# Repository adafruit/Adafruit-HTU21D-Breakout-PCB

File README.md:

## Adafruit HTU21D Breakout PCB
<a href="http://www.adafruit.com/products/1899"><br/>
<a href="http://www.adafruit.com/products/1899"><br/>
Click here to purchase one from the Adafruit shop</a>

The HTU21D-F Temperature + Humidity Sensor - the best way to prove the weatherman wrong!

This I2C digital humidity sensor is an accurate and intelligent alternative to the much simpler Humidity and Temperature Sensor - SHT15 Breakout It has a typical accuracy of ±2% with an operating range that's optimized from 5% to 95% RH. Operation outside this range is still possible - just the accuracy might drop a bit. The temperature output has an accuracy of ±1°C from -30~90°C. If you're looking to measure temperature more accurately, we recommend the MCP9808 High Accuracy I2C Temperature Sensor Breakout Board.

To get you going fast, we spun up a custom made PCB in the STEMMA QT form factor, making them easy to interface with. The STEMMA QT connectors on either side are compatible with the SparkFun Qwiic I2C connectors. This allows you to make solderless connections between your development board and the HTU21Ds or to chain them with a wide range of other sensors and accessories using a compatible cable. QT Cable is not included, but we have a variety in the shop.

PCB files for the Adafruit HTU21D Breakout. The format is EagleCAD schematic and board layout
- https://www.adafruit.com/products/1899

### License

Adafruit invests time and resources providing this open source design, please support Adafruit and open-source hardware by purchasing products from [Adafruit](https://www.adafruit.com)!

All text above must be included in any redistribution

Designed by Limor Fried/Ladyada for Adafruit Industries.
Creative Commons Attribution/Share-Alike, all text above must be included in any redistribution. 
See license.txt for additional information.

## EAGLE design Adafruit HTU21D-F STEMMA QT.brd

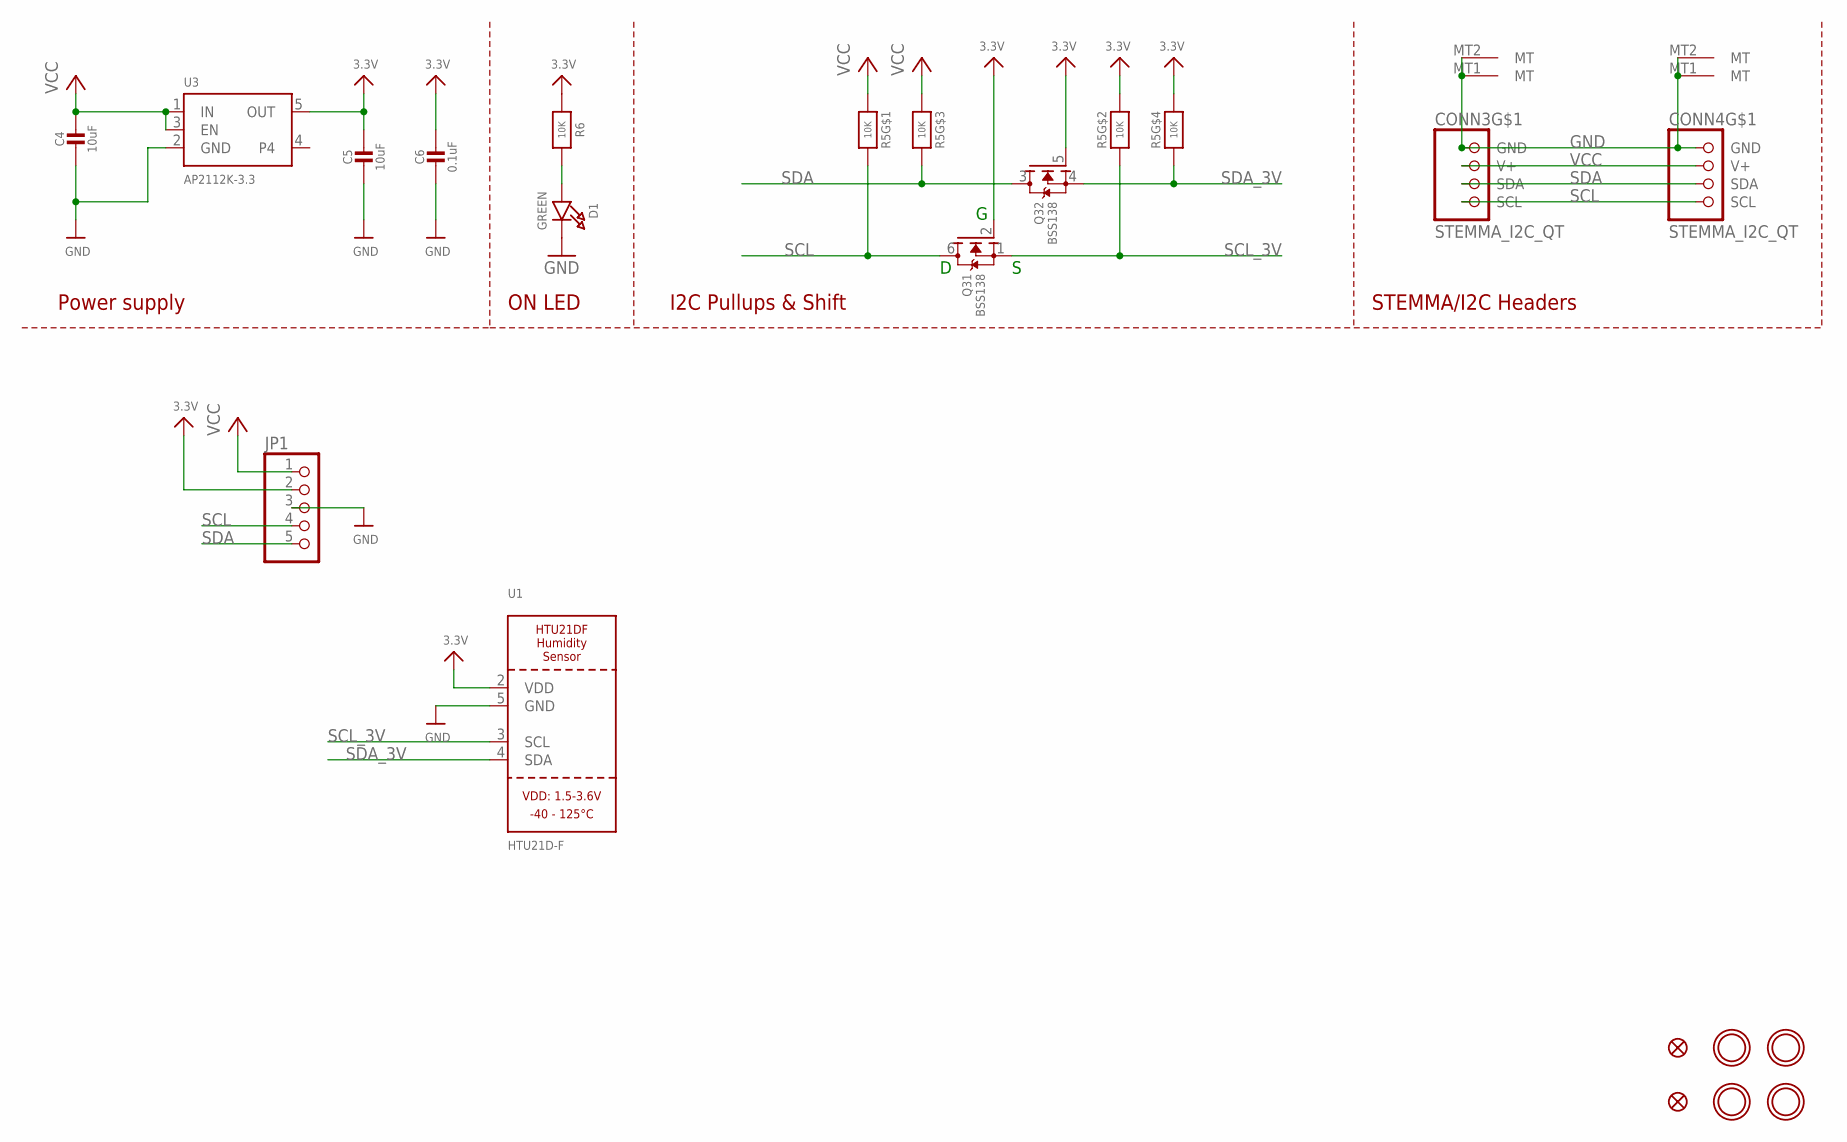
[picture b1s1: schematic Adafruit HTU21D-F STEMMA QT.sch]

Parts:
C4, C5: 10uF; 0805-NO
C6: 0.1uF; 0603-NO
CONN3, CONN4: STEMMA_I2C_QT; JST_SH4
D1: GREEN; CHIPLED_0603_NOOUTLINE
FID3, FID4: FIDUCIAL_1MM
JP1: HEADER-1X570MIL; 1X05_ROUND_70
Q3: BSS138; SOT363
R5: 10K; RESPACK_4X0603
R6: 10K; 0603-NO
U1: HTU21D-F; HTU21DF
U3: AP2112K-3.3; SOT23-5
U$19, U$20, U$22, U$25: MOUNTINGHOLE2.5; MOUNTINGHOLE_2.5_PLATED

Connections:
3.3V: C5.1, C6.1, JP1.2, Q3.2 (G), Q3.5 (G), R5.2 (1), R5.4 (1), R6.1, U1.2 (VDD), U3.5 (OUT)
GND: C4.2, C5.2, C6.2, CONN3.1 (GND), CONN3.MT1 (MT), CONN3.MT2 (MT), CONN4.1 (GND), CONN4.MT1 (MT), CONN4.MT2 (MT), D1.C, JP1.3, U1.5 (GND), U3.2 (GND)
unnamed: D1.A, R6.2
SCL: CONN3.4 (SCL), CONN4.4 (SCL), JP1.4, Q3.6 (D), R5.8 (2)
SCL_3V: Q3.1 (S), R5.7 (2), U1.3 (SCL)
SDA: CONN3.3 (SDA), CONN4.3 (SDA), JP1.5, Q3.3 (D), R5.6 (2)
SDA_3V: Q3.4 (S), R5.5 (2), U1.4 (SDA)
VCC: C4.1, CONN3.2 (V+), CONN4.2 (V+), JP1.1, R5.1, R5.3 (1), U3.1 (IN), U3.3 (EN)

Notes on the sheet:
I2C Pullups & Shift
STEMMA/I2C Headers
ON LED
Power supply

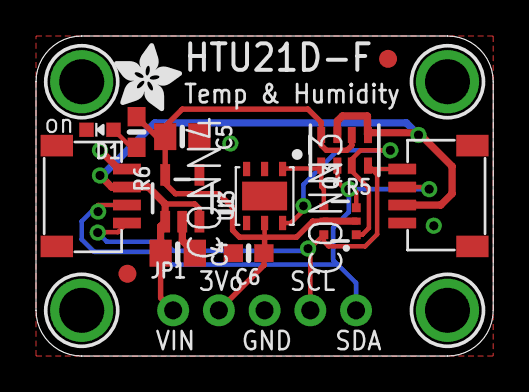
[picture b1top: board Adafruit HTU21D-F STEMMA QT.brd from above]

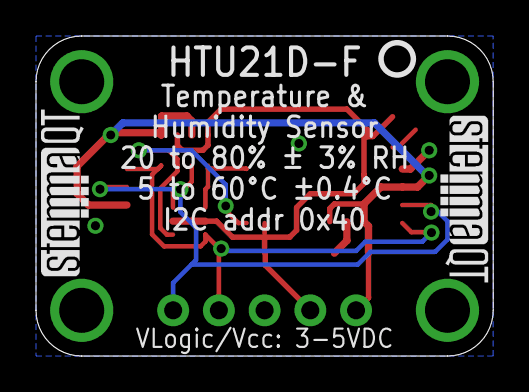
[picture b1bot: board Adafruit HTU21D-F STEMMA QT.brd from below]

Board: 2 copper layers, 25.4 x 17.8 mm, 22 parts (3 on the bottom side), 8 nets.

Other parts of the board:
U$28: ADAFRUIT_3.5MM
U$29: PCBFEAT-REV-040
U$30, U$31: STEMMAQT

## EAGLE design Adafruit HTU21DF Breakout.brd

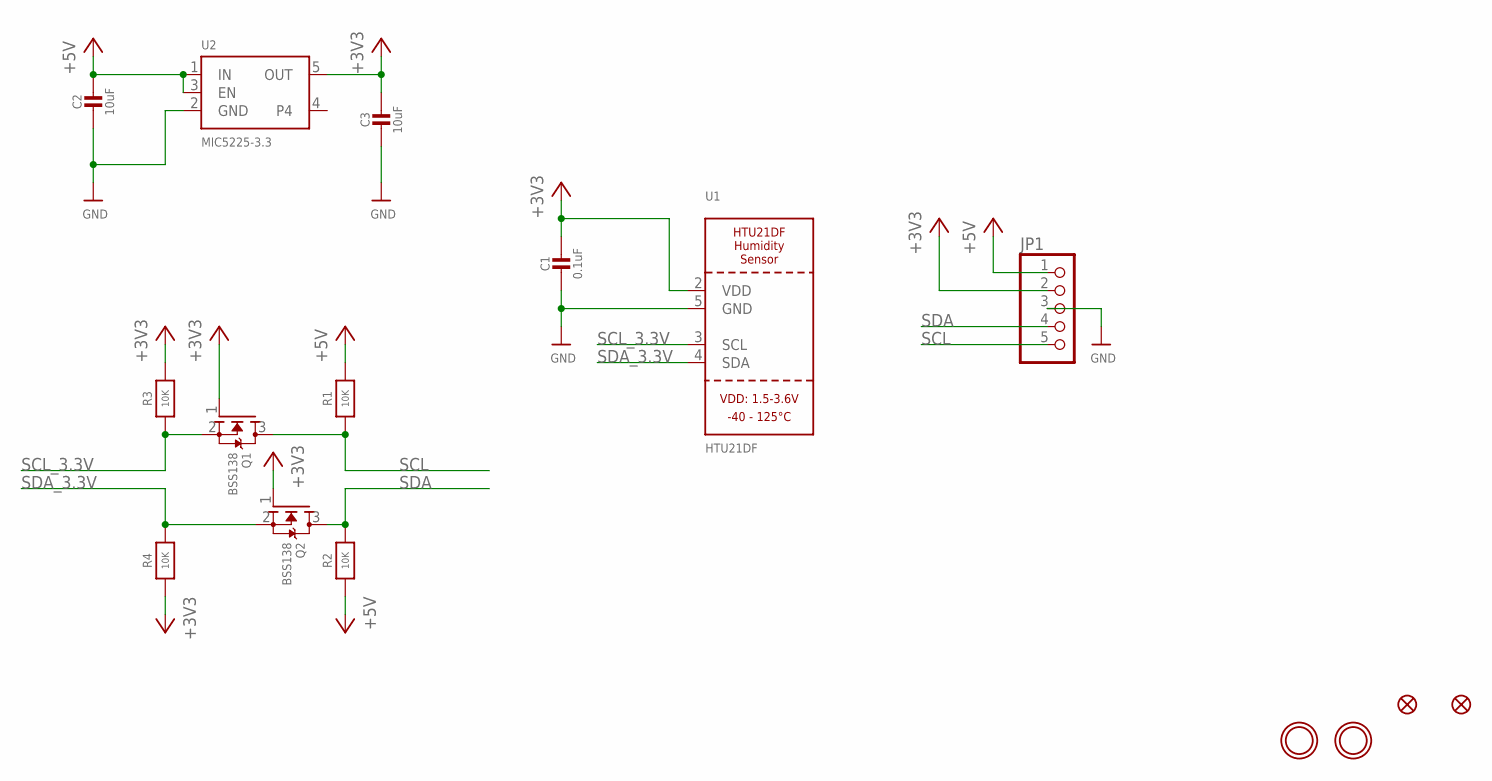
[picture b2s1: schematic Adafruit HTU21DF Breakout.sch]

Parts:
C1: 0.1uF; 0805-NO
C2, C3: 10uF; 0805-NO
FID1, FID2: FIDUCIAL""; FIDUCIAL_1MM
JP1: HEADER-1X570MIL; 1X05_ROUND_70
Q1, Q2: BSS138; SOT23-WIDE
R1, R2, R3, R4: 10K; 0805-NO
U1: HTU21DF
U2: MIC5225-3.3; SOT23-5
U$3, U$4: MOUNTINGHOLE2.5; MOUNTINGHOLE_2.5_PLATED

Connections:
+3V3: C1.1, C3.1, JP1.2, Q1.1 (G), Q2.1 (G), R3.2, R4.1, U1.2 (VDD), U2.5 (OUT)
GND: C1.2, C2.2, C3.2, JP1.3, U1.5 (GND), U2.2 (GND)
SCL: JP1.5, Q1.3 (D), R1.1
SCL_3.3V: Q1.2 (S), R3.1, U1.3 (SCL)
SDA: JP1.4, Q2.3 (D), R2.2
SDA_3.3V: Q2.2 (S), R4.2, U1.4 (SDA)
VIN: C2.1, JP1.1, R1.2, R2.1, U2.1 (IN), U2.3 (EN)

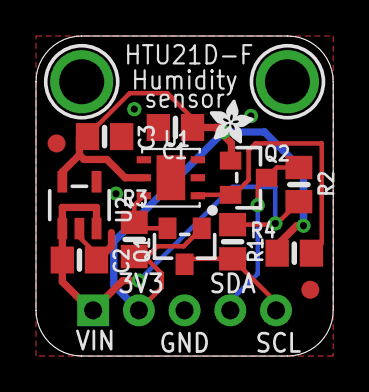
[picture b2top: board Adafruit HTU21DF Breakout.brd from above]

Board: 2 copper layers, 16.5 x 17.8 mm, 18 parts (1 on the bottom side), 7 nets.

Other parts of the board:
U$1: ADAFRUIT_3.5MM
U$8: ADAFRUIT_2.5MM

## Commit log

2016-08-24 init
2021-04-14 Adding STEMMA QT

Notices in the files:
parts and their libraries:
microbuilder: This work is placed in the public domain, and may be freely used for commercial and non-commercial work with the following conditions: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
